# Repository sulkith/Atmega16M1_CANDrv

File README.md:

# Atmega16M1_CANDrv

A CAN Driver for the Atmega 16M1 this Driver supports standard 11Bit Identifier and Interrupt driven receiving.<br>
The driver Parts are:

* CANDrv.cpp
* CANDrv.h

The other files are a reference Project for the Driver and the provided Board,<br>
which reads out the Engine Temperature on my BMW E90.<br>
The Can Message 0x130 is sent by the car on the OBD CAN.<br>
This Message encodes the T15 Signal, which is not present on the OBD port of the E90.<br>
Therefore this Message is used to sent the Board to sleep.

# ATMEGA16M1Board

A small PCB with an Atmega 16M1 to test and use the Driver.<br>
The assembled Board looks like this:<br>
.jpg)
.jpg)
.jpg)
The board in action can be seen here:<br>
.jpg)
.jpg)
.jpg)

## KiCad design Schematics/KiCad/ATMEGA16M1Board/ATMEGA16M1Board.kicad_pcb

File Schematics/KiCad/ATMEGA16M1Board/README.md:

# Errata to the Schematics

Schematics from commit adee088dd9ad20461ed7a09ecef526a60e1ee473
* Important fix:<br>
  connect +5VPin from Display IC3-PIN3 to +5VPin from FTDI IC2-PIN3.<br>
  no fixed board yet
* other fixes: <br>
  for Display Operation connect R4 to Display CS IC3-PIN7.<br>
  no fixed board yet
* for Wakeup: <br>
  remove Q4 and R10. Connect RXCAN of MCP2551 U2-PIN4 to PWM1A1.<br>
  no fixed schematics yet<br>
  no fixed board yet<br>
  
The fixes are marked on the Pictures below:

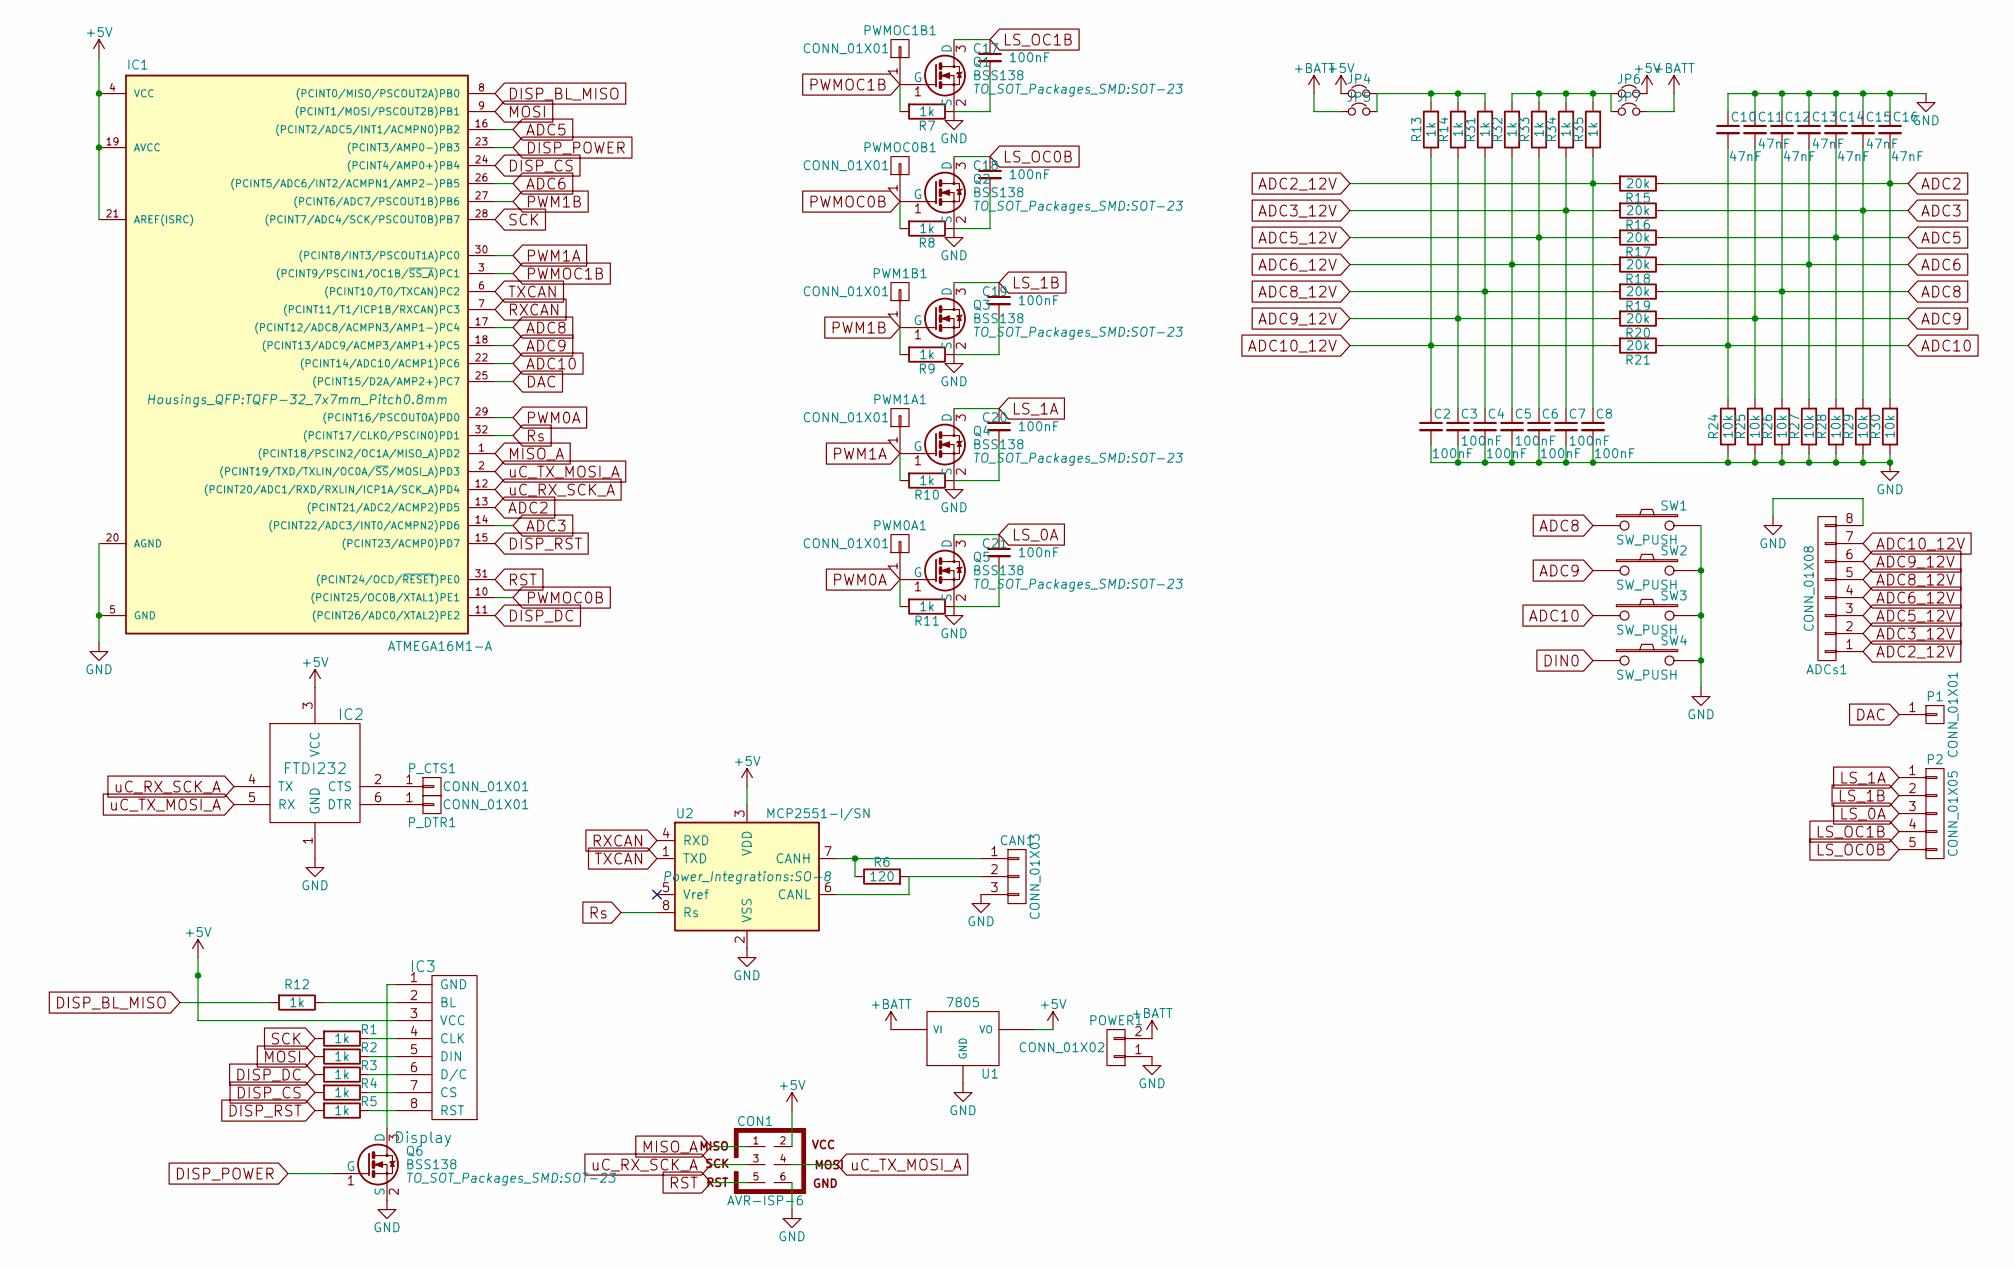
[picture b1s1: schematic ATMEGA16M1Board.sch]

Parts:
ADCs1: CONN_01X08; Pin_Header_Straight_1x08
C2, C3, C4, C5, C6, C7, C8, C17, C18, C19, C20, C21: 100nF; C_0603_HandSoldering
C10, C11, C12, C13, C14, C15, C16: 47nF; C_0603_HandSoldering
CAN1: CONN_01X03; Pin_Header_Straight_1x03
CON1: AVR-ISP-6; Pin_Header_Straight_2x03
IC1: ATMEGA16M1-A; TQFP-32_7x7mm_Pitch0.8mm
IC2: FTDI232; Pin_Header_Straight_1x06
IC3: Display; Pin_Header_Straight_1x08
JP4, JP5, JP6, JP7: Jumper_NC_Small; R_0201
P1: CONN_01X01; PINTST
P2: CONN_01X05; Pin_Header_Straight_1x05
POWER1: CONN_01X02; Pin_Header_Straight_1x02
PWM0A1, PWM1A1, PWM1B1: CONN_01X01; PINTST
PWMOC0B1, PWMOC1B1: CONN_01X01; PINTST
P_CTS1: CONN_01X01; Pin_Header_Straight_1x01
P_DTR1: CONN_01X01; Pin_Header_Straight_1x01
Q1, Q2, Q3, Q4, Q5, Q6: BSS138; SOT-23
R1, R2, R3, R4, R5, R7, R8, R9, R10, R11, R12, R13, R14, R31, R32, R33, R34, R35: 1k; R_0603_HandSoldering
R6: 120; R_0603_HandSoldering
R15, R16, R17, R18, R19, R20, R21: 20k; R_0603_HandSoldering
R24, R25, R26, R27, R28, R29, R30: 10k; R_0603_HandSoldering
SW1, SW2, SW3, SW4: SW_PUSH; SW_PUSH_6mm
U1: 7805; TO-220_Vertical
U2: MCP2551-I/SN; SO-8

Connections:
+5V: CON1.2, IC1.4 (VCC), IC1.19 (AVCC), IC1.21 (AREF(ISRC)), IC2.3 (VCC), IC3.3 (VCC), JP4.1, JP6.2, U1.3 (VO), U2.3 (VDD); also elsewhere on the board
+BATT: JP5.1, JP7.2, POWER1.2, U1.1 (VI)
ADC2: C16.2, IC1.13 ((PCINT21/ADC2/ACMP2)PD5), R15.1, R30.2
ADC2_12V: ADCs1.1, C8.1, R15.2, R35.1
ADC3: C15.2, IC1.14 ((PCINT22/ADC3/INT0/ACMPN2)PD6), R16.1, R29.2
ADC3_12V: ADCs1.2, C7.1, R16.2, R34.1
ADC5: C14.2, IC1.16 ((PCINT2/ADC5/INT1/ACMPN0)PB2), R17.1, R28.2
ADC5_12V: ADCs1.3, C6.1, R17.2, R33.1
ADC6: C13.2, IC1.26 ((PCINT5/ADC6/INT2/ACMPN1/AMP2-)PB5), R18.1, R27.2
ADC6_12V: ADCs1.4, C5.1, R18.2, R32.1
ADC8: C12.2, IC1.17 ((PCINT12/ADC8/ACMPN3/AMP1-)PC4), R19.1, R26.2, SW1.1
ADC8_12V: ADCs1.5, C4.1, R19.2, R31.1
ADC9: C11.2, IC1.18 ((PCINT13/ADC9/ACMP3/AMP1+)PC5), R20.1, R25.2, SW2.1
ADC9_12V: ADCs1.6, C3.1, R14.1, R20.2
ADC10: C10.2, IC1.22 ((PCINT14/ADC10/ACMP1)PC6), R21.1, R24.2, SW3.1
ADC10_12V: ADCs1.7, C2.1, R13.1, R21.2
DAC: IC1.25 ((PCINT15/D2A/AMP2+)PC7), P1.1
DIN0: SW4.1
DISP_BL_MISO: IC1.8 ((PCINT0/MISO/PSCOUT2A)PB0), R12.2
DISP_CS: IC1.24 ((PCINT4/AMP0+)PB4), R4.2
DISP_DC: IC1.11 ((PCINT26/ADC0/XTAL2)PE2), R3.2
DISP_POWER: IC1.23 ((PCINT3/AMP0-)PB3), Q6.1 (G)
DISP_RST: IC1.15 ((PCINT23/ACMP0)PD7), R5.2
GND: ADCs1.8, C2.2, C3.2, C4.2, C5.2, C6.2, C7.2, C8.2, C10.1, C11.1, C12.1, C13.1, C14.1, C15.1, C16.1, C17.2, C18.2, C19.2, C20.2, C21.2, CAN1.3, CON1.6, IC1.5 (GND), IC1.20 (AGND), IC2.1 (GND), POWER1.1, Q1.2 (S), Q2.2 (S), Q3.2 (S), Q4.2 (S), Q5.2 (S), Q6.2 (S), R7.1, R8.1, R9.1, R10.1, R11.1, R24.1, R25.1, R26.1, R27.1, R28.1, R29.1, R30.1, SW1.2, SW2.2, SW3.2, SW4.2, U1.2 (GND), U2.2 (VSS); also elsewhere on the board
LS_0A: C21.1, P2.3, Q5.3 (D)
LS_1A: C20.1, P2.1, Q4.3 (D)
LS_1B: C19.1, P2.2, Q3.3 (D)
LS_OC0B: C18.1, P2.5, Q2.3 (D)
LS_OC1B: C17.1, P2.4, Q1.3 (D)
MISO_A: CON1.1, IC1.1 ((PCINT18/PSCIN2/OC1A/MISO_A)PD2); also elsewhere on the board
MOSI: IC1.9 ((PCINT1/MOSI/PSCOUT2B)PB1), R2.2
unnamed: CAN1.1, R6.1, U2.7 (CANH)
unnamed: CAN1.2, R6.2, U2.6 (CANL)
unnamed: IC2.2 (CTS), P_CTS1.1
unnamed: IC2.6 (DTR), P_DTR1.1
unnamed: IC3.1 (GND), Q6.3 (D)
unnamed: IC3.2 (BL), R12.1
unnamed: IC3.4 (CLK), R1.1
unnamed: IC3.5 (DIN), R2.1
unnamed: IC3.6 (D/C), R3.1
unnamed: IC3.7 (CS), R4.1
unnamed: IC3.8 (RST), R5.1
unnamed: JP4.2, JP5.2, R13.2, R14.2, R31.2
unnamed: JP6.1, JP7.1, R32.2, R33.2, R34.2, R35.2
PWM0A: IC1.29 ((PCINT16/PSCOUT0A)PD0), PWM0A1.1, Q5.1 (G), R11.2
PWM1A: IC1.30 ((PCINT8/INT3/PSCOUT1A)PC0), PWM1A1.1, Q4.1 (G), R10.2
PWM1B: IC1.27 ((PCINT6/ADC7/PSCOUT1B)PB6), PWM1B1.1, Q3.1 (G), R9.2
PWMOC0B: IC1.10 ((PCINT25/OC0B/XTAL1)PE1), PWMOC0B1.1, Q2.1 (G), R8.2
PWMOC1B: IC1.3 ((PCINT9/PSCIN1/OC1B/~SS_A~)PC1), PWMOC1B1.1, Q1.1 (G), R7.2
RST: CON1.5, IC1.31 ((PCINT24/OCD/~RESET~)PE0); also elsewhere on the board
RXCAN: IC1.7 ((PCINT11/T1/ICP1B/RXCAN)PC3), U2.4 (RXD)
Rs: IC1.32 ((PCINT17/CLKO/PSCIN0)PD1), U2.8 (Rs)
SCK: IC1.28 ((PCINT7/ADC4/SCK/PSCOUT0B)PB7), R1.2
TXCAN: IC1.6 ((PCINT10/T0/TXCAN)PC2), U2.1 (TXD)
uC_RX_SCK_A: CON1.3, IC1.12 ((PCINT20/ADC1/RXD/RXLIN/ICP1A/SCK_A)PD4), IC2.4 (TX); also elsewhere on the board
uC_TX_MOSI_A: CON1.4, IC1.2 ((PCINT19/TXD/TXLIN/OC0A/~SS~/MOSI_A)PD3), IC2.5 (RX); also elsewhere on the board

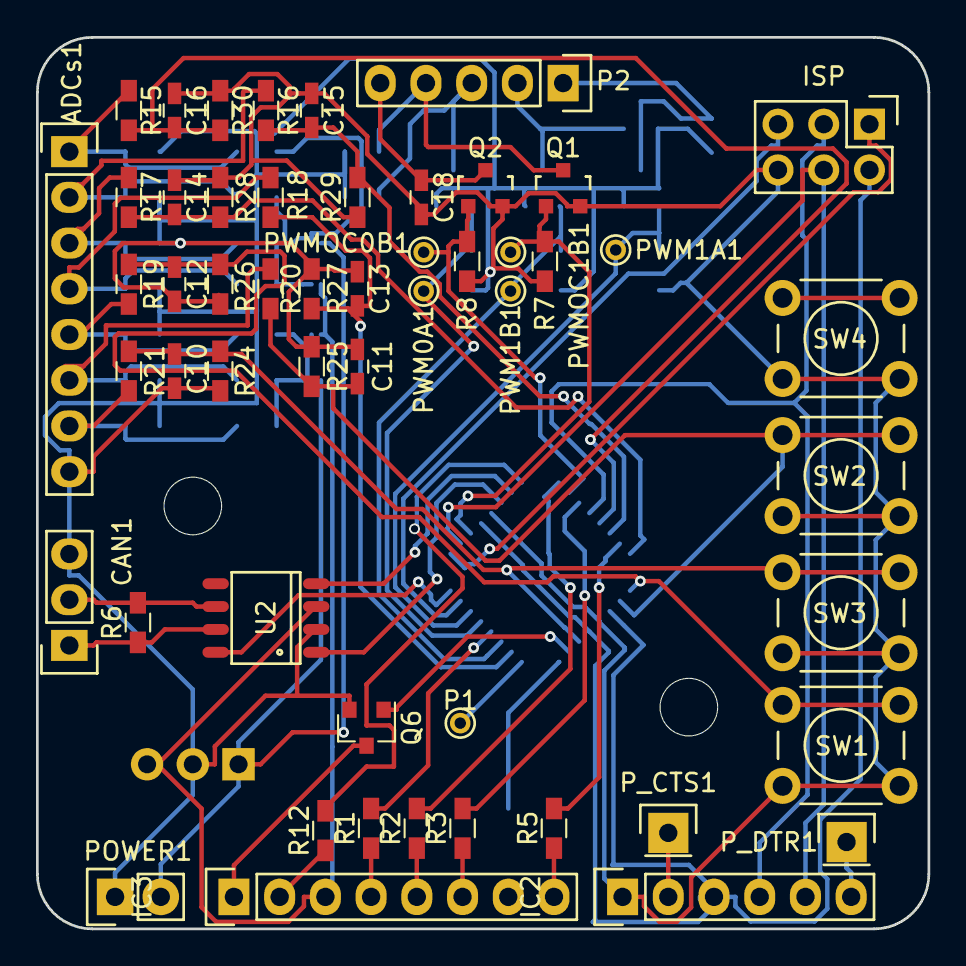
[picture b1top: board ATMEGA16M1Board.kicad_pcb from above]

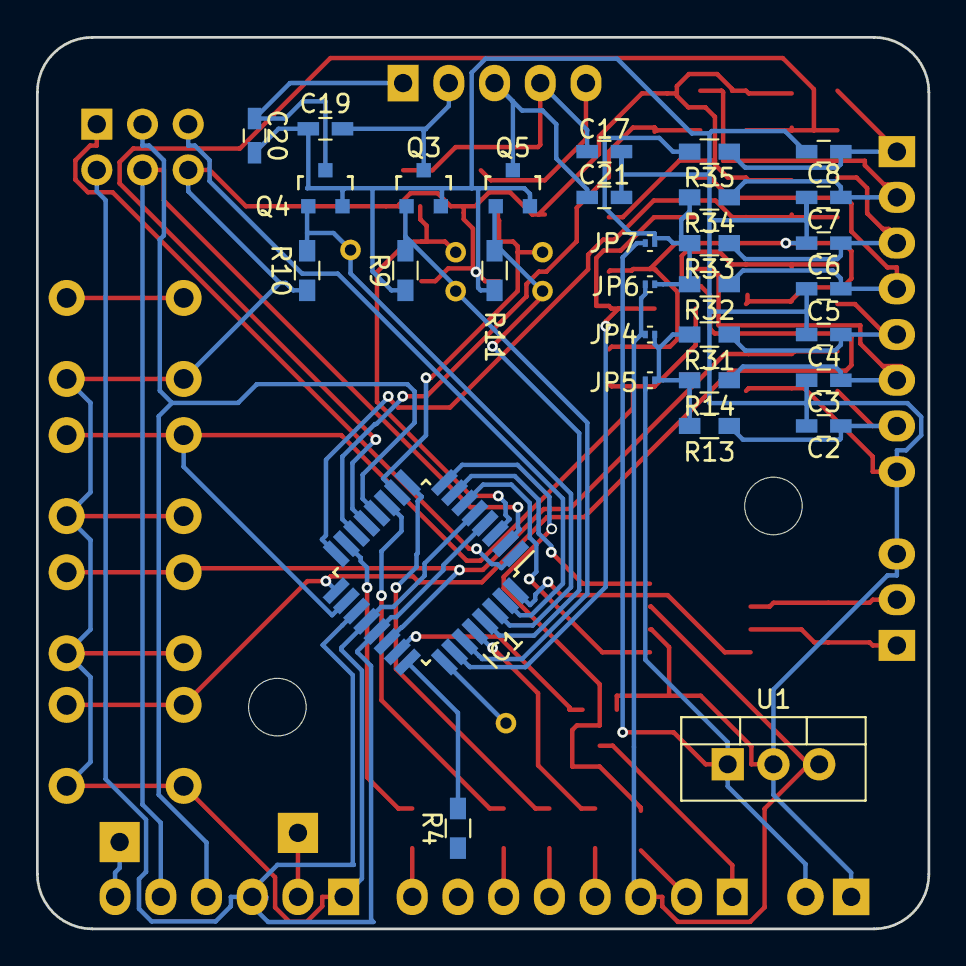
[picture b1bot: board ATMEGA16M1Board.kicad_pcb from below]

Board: 2 copper layers, 49.5 x 49.5 mm, 84 parts (31 on the bottom side), 55 nets.

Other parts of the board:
ISP: AVR-ISP-6; Pin_Header_Straight_2x03

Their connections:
+5V: ISP.2; also elsewhere on the board
GND: ISP.6; also elsewhere on the board
MISO_A: ISP.1; also elsewhere on the board
RST: ISP.5; also elsewhere on the board
uC_RX_SCK_A: ISP.3; also elsewhere on the board
uC_TX_MOSI_A: ISP.4; also elsewhere on the board

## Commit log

2016-12-11 Initial import from local repository
2016-12-11 removed latex directory
2016-12-23 introduced a MessageValidator, to take care of timeouts.
2016-12-24 Added Display. Improved Message Validator
2016-12-24 cleanup
2016-12-27 Added Shutdown functionality. Added some defines to change the color on the Display.
2016-12-30 changed display color. removed test code
2017-03-02 Renamed Display Pin definitions Added Display Powersave Function Added separate pinning File
2017-03-02 improved Shutdown concept. Added CAN_Active MessageValidator
2017-03-02 Added Schematics and PCB. PCB is NOT tested yet.
2017-03-02 Gerber.zip File for ordering the PCBs
2017-03-02 Added PCB before Autorouter. Pay attention to changes in the Schematics!!!
2017-03-02 removed the zip to keep the Project clean.
2017-03-02 Test
2017-03-03 Project Cleanup. Added SCState to the display output. optimized Display driver.
2017-03-07 Added Arduino Plugin
2017-03-07 Added Support for Atmega 32M1 and 64M1
2017-03-07 Removed Trailing zeros from tmot
2017-03-16 Create README.md
    Added Errata document
2017-03-16 Update README.md
    updated Schematics readme
2017-03-16 modified pinning for the PCB. enabled Shutdown. Worked on a reworked PCB. See errata of the schematics for details.
2017-03-17 added more aggressive shutdown
2017-03-17 resolved a nasty bug in the mask generation i was not initialized.
2017-03-17 Added a delay to the loop to keep the load on the ECU dowm
2017-03-17 Added Pictures of the board
2017-03-17 Added pictures to the readme
2017-03-19 optimized Display Driver. its easier to change the Layout now.
2017-03-19 reordered Documentation
2017-03-19 added a Feature to get the Status of a Message. Generated Documentation.
2017-03-19 Added a Message Scheduler to keep the controller running and reduce Busload. Additionally it is possible to request more than one PID with the scheduler.
2017-03-19 Added a Readme.md in the Software to keep track of supported PIDs
2017-03-19 Fixed build error
2017-04-05 Added Engine Load to the Display. Added a Welcome Message as Startup screen. Smoothed the corners of the Bar graphs.
